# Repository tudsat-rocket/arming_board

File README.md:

# Arming board

This repo contains the hardware design for the new arming board for our project Zepyhr. The arming board works with a flip-flop and a MOSFET. An external arming signal can set the flip-flop's state, which controls the MOSFETs.

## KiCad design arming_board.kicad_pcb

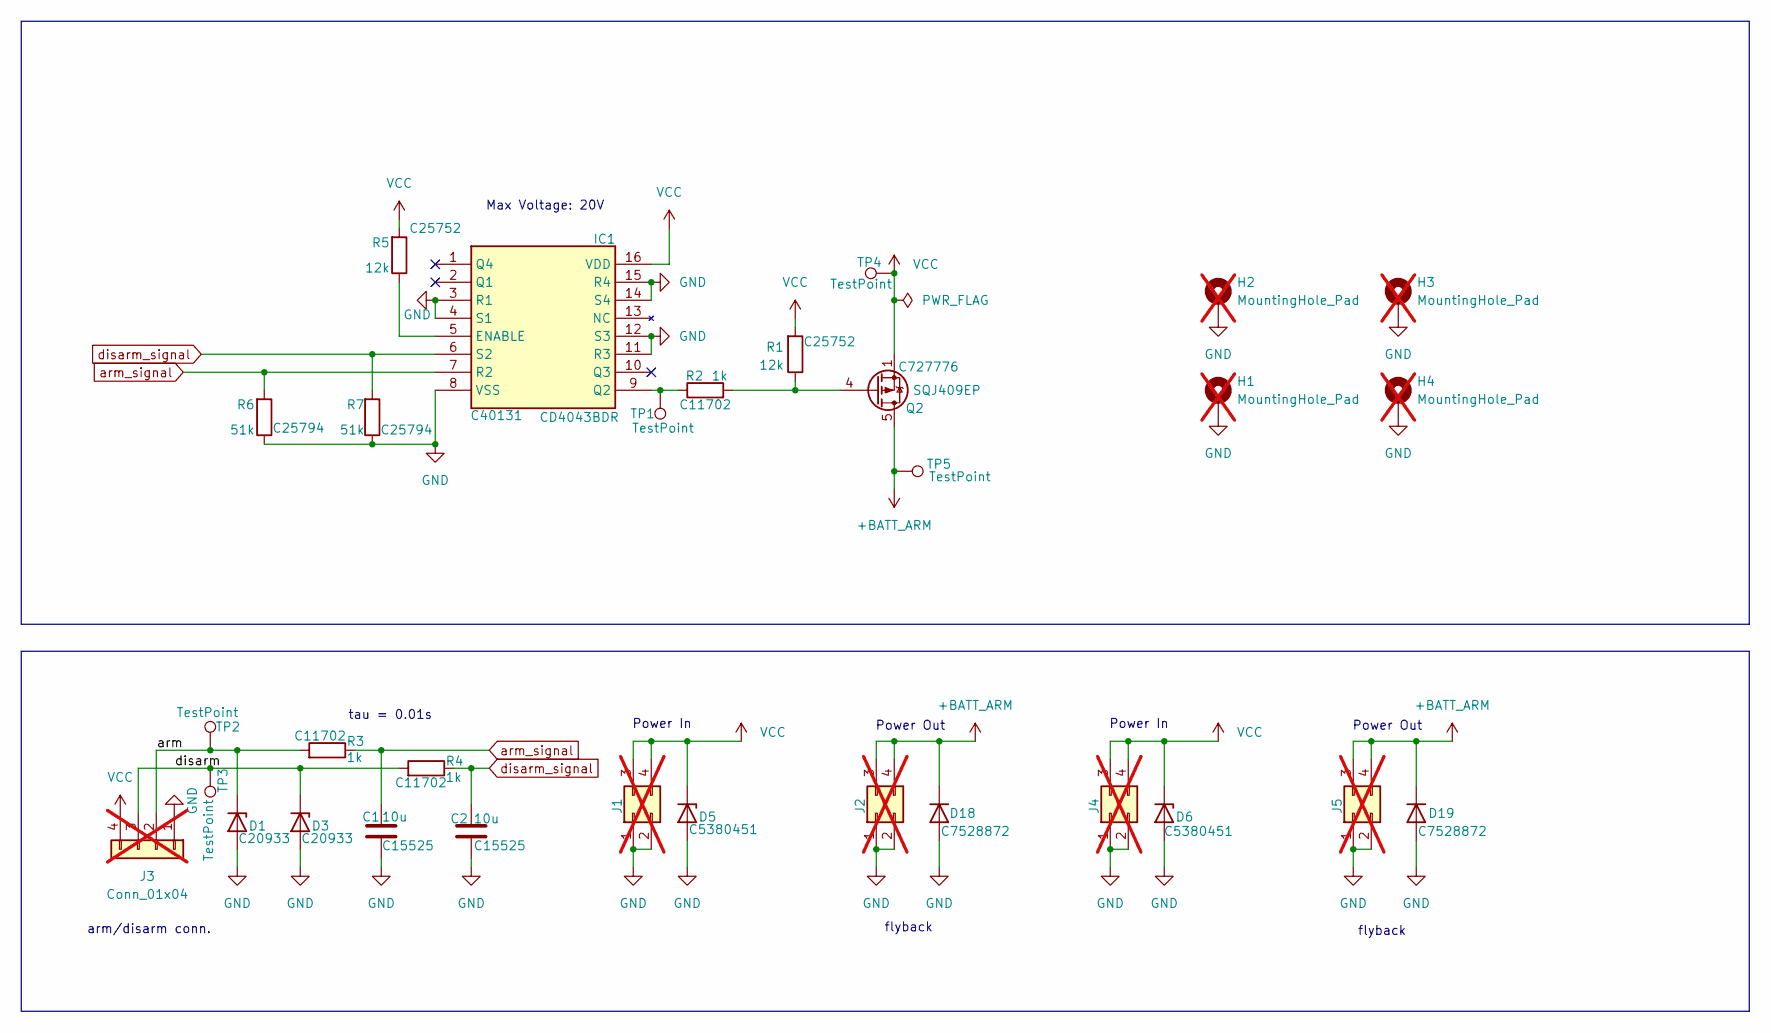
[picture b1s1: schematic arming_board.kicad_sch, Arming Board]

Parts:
C1, C2: 10u; C_0402_1005Metric; LCSC C15525
D1, D3: ESD5Zxx; D_SOD-523; LCSC C20933
D5, D6: TS1811LD-CX; D_SOD-523; LCSC C5380451
D18, D19: D; D_SOD-323_HandSoldering; LCSC# C7528872
H1, H2, H3, H4: MountingHole_Pad; MountingHole_3.2mm_M3_DIN965_Pad_TopBottom; not fitted
IC1: CD4043BDR; SOIC-16_4.55x10.3mm_P1.27mm; Mouser Part Number 595-CD4043BDR
J1, J2, J4, J5: Molex_Micro-Fit_3.0_43045-0400_2x02_P3.00mm_Horizontal; LCSC# x; not fitted
J3: Conn_01x04; Molex_Micro-Fit_3.0_43650-0400_1x04_P3.00mm_Horizontal; not fitted
Q2: SQJ409EP; PowerPAK_SO-8L_Single; LCSC C727776
R1, R5: 12k; R_0402_1005Metric_Pad0.72x0.64mm_HandSolder; LCSC C25752
R2, R3, R4: 1k; R_0402_1005Metric_Pad0.72x0.64mm_HandSolder; LCSC C11702
R6, R7: 51k; R_0402_1005Metric_Pad0.72x0.64mm_HandSolder; LCSC C25794
TP1, TP2, TP3, TP4, TP5: TestPoint; TestPoint_Pad_D1.0mm

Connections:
+BATT_ARM: D18.1 (K), D19.1 (K), J2.3, J2.4, J5.3, J5.4, Q2.5 (D), TP5.1 (1_1)
/arm: D1.1 (K), J3.2, R3.2, TP2.1 (1_1)
/disarm: D3.1 (K), J3.3, R4.2, TP3.1 (1_1)
GND: C1.2, C2.2, D1.2 (A), D3.2 (A), D5.2 (A), D6.2 (A), D18.2 (A), D19.2 (A), H1.1 (1_1), H2.1 (1_1), H3.1 (1_1), H4.1 (1_1), IC1.3 (R1), IC1.4 (S1), IC1.8 (VSS), IC1.11 (R3), IC1.12 (S3), IC1.14 (S4), IC1.15 (R4), J1.1, J1.2, J2.1, J2.2, J3.1, J4.1, J4.2, J5.1, J5.2, R6.1, R7.1
unnamed: IC1.5 (ENABLE), R5.1
unnamed: IC1.9 (Q2), R2.1, TP1.1 (1_1)
unnamed: Q2.4 (G), R1.1, R2.2
VCC: D5.1 (K), D6.1 (K), IC1.16 (VDD), J1.3, J1.4, J3.4, J4.3, J4.4, Q2.1 (S), Q2.2 (S), Q2.3 (S), R1.2, R5.2, TP4.1 (1_1)
arm_signal: C1.1, IC1.7 (R2), R3.1, R6.2
disarm_signal: C2.1, IC1.6 (S2), R4.1, R7.2

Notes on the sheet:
Power Out
flyback
Power In
Max Voltage: 20V
arm/disarm conn.
tau = 0.01s

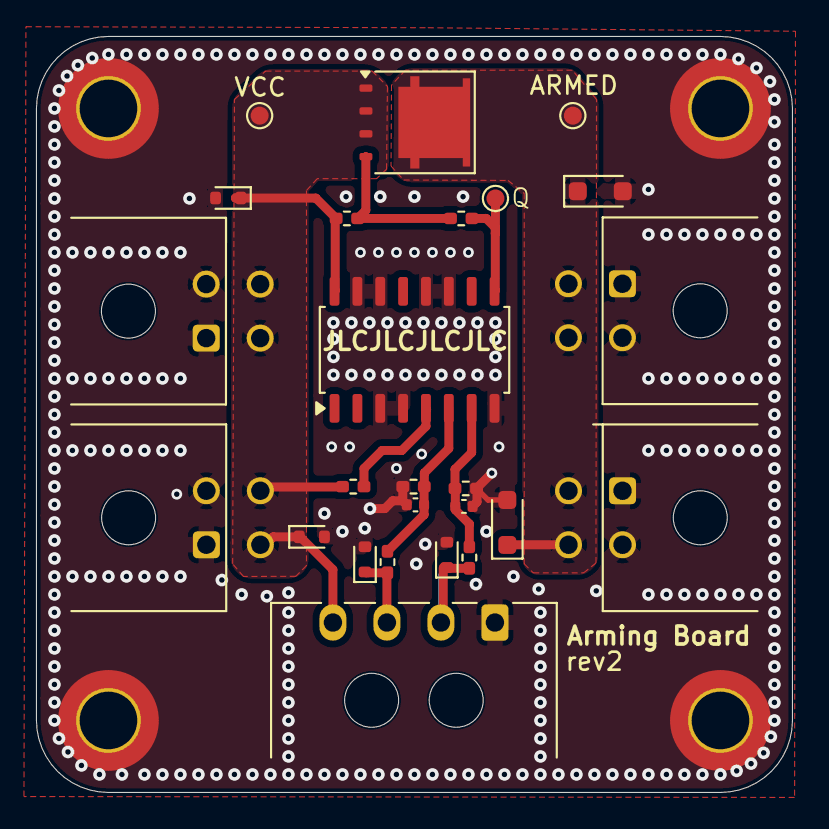
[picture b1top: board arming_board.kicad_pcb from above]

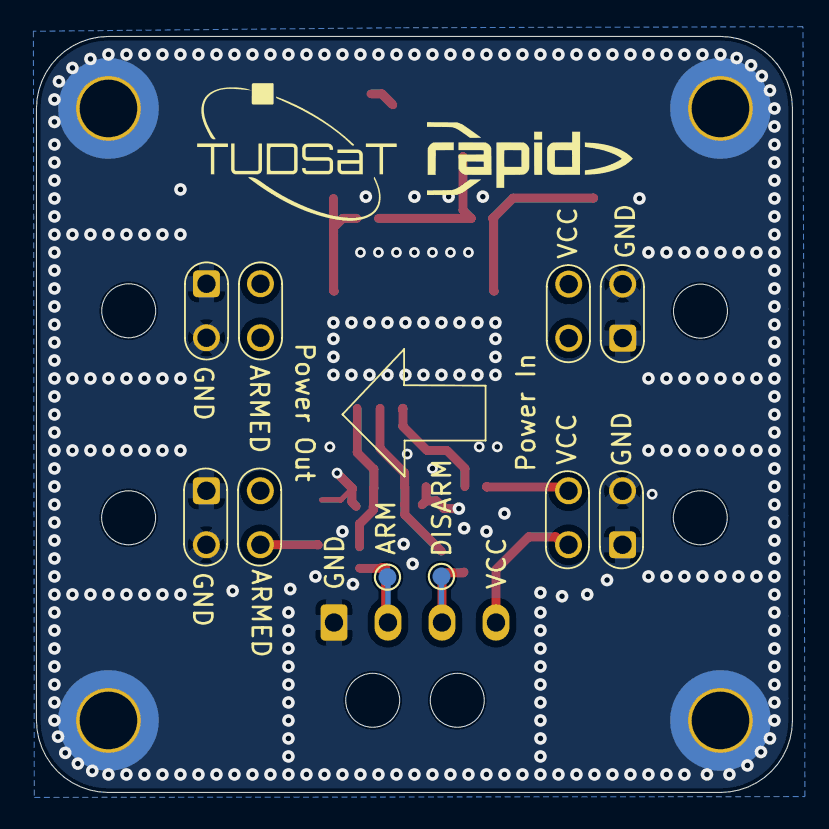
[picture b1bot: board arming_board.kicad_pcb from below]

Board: 2 copper layers, 42.0 x 42.0 mm, 31 parts (2 on the bottom side), 10 nets.

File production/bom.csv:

Designator,Footprint,Quantity,Value,LCSC Part #
"C1, C2",0402,2,10u,C15525
"D1, D3",D_SOD-523,2,ESD5Zxx,C20933
"D18, D19",D_SOD-323_HandSoldering,2,D,
"D5, D6",D_SOD-523,2,TS1811LD-CX,C5380451
IC1,SOIC-16_4.55x10.3mm_P1.27mm,1,CD4043BDR,C40131
Q2,PowerPAK_SO-8L_Single,1,SQJ409EP,C727776
"R1, R5",0402,2,12k,C25752
"R2, R3, R4",0402,3,1k,C11702
"R6, R7",0402,2,51k,C25794
"TP1, TP2, TP3, TP4, TP5",TestPoint_Pad_D1.0mm,5,TestPoint,

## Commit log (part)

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2026-06-19 Basic routing and fixes
2026-06-22 improve routing
2026-06-23 check parts, replace mosfet
2026-06-26 improve silkscreen
2026-06-28 change flipflop footprint
2026-06-29 order version
